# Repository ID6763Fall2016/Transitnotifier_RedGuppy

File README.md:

# Transitnotifier_RedGuppy

This is the transit notifier project called Buzz Clock.
You will need the following hardware and software to build the Buzz Clock: 

Hardware:
<ul>
<li>ESP8266 x 1 (adafruit Huzzah breakout for the PCB we used)</li> 
<li>NeoPixel strip x 1 (60 neoPixels.  You can use less but you'll need to modify the code heavily)</li>
<li>Battery x 1 (or a USB 5 volt power supply with power and ground connections</li>
<li>Resistor x 2 (10k and 470R)</li>
<li>Capacitor x 1 (1000U 16v or 24v) </li>
<li>Push button x 1</li>
</ul>

Software:
<ul>
<li>Adafruit NeoPixel library</li>
<li>WiFi Client Secure library</li>
<li>TinyXML library</li>
</ul>

The working code resides in the NextBusGT folder. After connecting the hardwares together and connecting ESP8266 to your laptop, you need to modify the code with your wifi SSID and Password then upload the code to the ESP8266 and it will start retrieve the data from the xml provided by http://gtbuses.herokuapp.com.

If you wish to make your own PCB instead of using a breadboard for the setup you can start with our CAD files in the WiFiNeoClock director.  We used KiCad to create the board.  Additional information on working with kiCad can be found at..
http://kicad-pcb.org/

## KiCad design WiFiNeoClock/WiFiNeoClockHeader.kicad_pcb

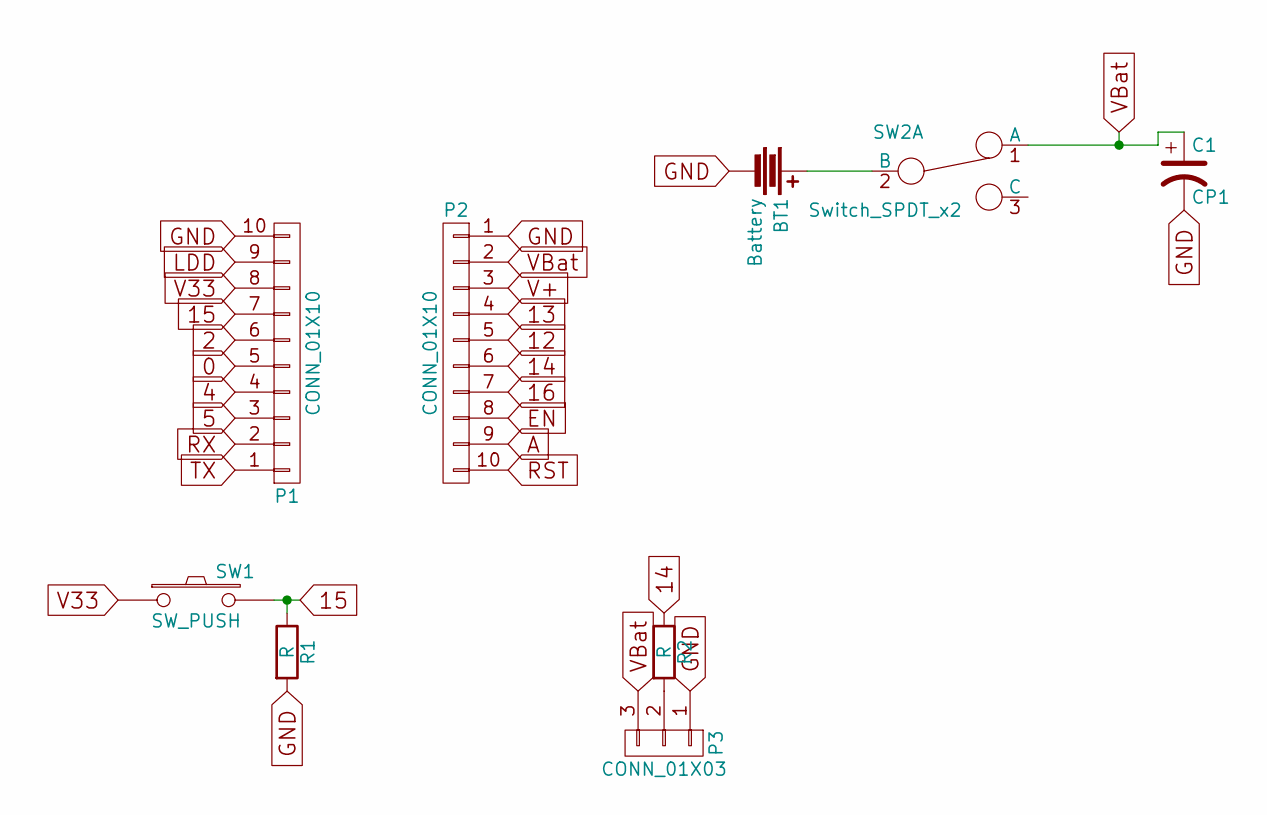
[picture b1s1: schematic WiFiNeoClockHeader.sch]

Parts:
BT1: Battery; Pin_Header_Straight_1x02
C1: CP1; C_Radial_D5_L11_P2.5
P1, P2: CONN_01X10; Pin_Header_Straight_1x10
P3: CONN_01X03; Pin_Header_Straight_1x03
R1, R2: R; Resistor_Horizontal_RM10mm
SW1: SW_PUSH; SW_PUSH_6mm
SW2: Switch_SPDT_x2; SW_NKK_G1xJP

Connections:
0: P1.5
2: P1.6
4: P1.4
5: P1.3
12: P2.5
13: P2.4
14: P2.6, R2.1
15: P1.7, R1.1, SW1.2
16: P2.7
A: P2.9
EN: P2.8
GND: BT1.2, C1.2, P1.10, P2.1, P3.1, R1.2
LDD: P1.9
unnamed: BT1.1, SW2.2 (B)
unnamed: P3.2, R2.2
RST: P2.10
RX: P1.2
TX: P1.1
V33: P1.8, SW1.1
V+: P2.3
VBat: C1.1, P2.2, P3.3, SW2.1 (A)

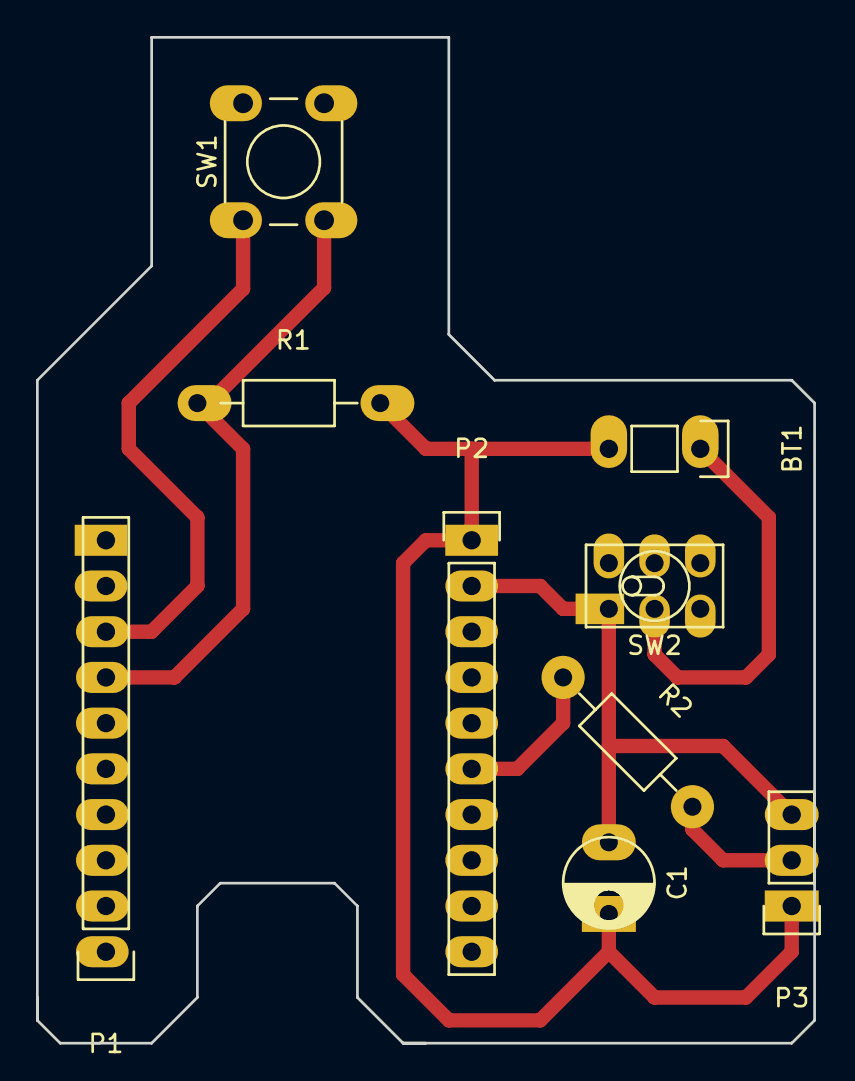
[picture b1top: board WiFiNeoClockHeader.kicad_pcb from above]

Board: 2 copper layers, 43.2 x 55.9 mm, 9 parts (0 on the bottom side), 7 nets.

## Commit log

2016-10-06 Added JSON Stream reading parser with hooks to act on keys
    example of queries for routes and pulling back location info.
2016-10-06 added libraries and examples for JSONstreaming parser
    Should use my version with the modified classes to get stuff done
2016-10-11 Add files via upload
    Design ideas
2016-10-12 Update HTTPSRequest.ino
    add parser
2016-10-12 Add files via upload
    extracts stops from xml
2016-10-12 Added clock starts and version of NextBus to target a specific stop for times
2016-10-13 Created a clock and Got flashing busses on the Neopixels
    Need to figure out a way to cache the bus times while refreshing the
    pixels faster
2016-10-17 "add pcb"
2016-10-18 working with NeoPixels
    working connection between gtbusses and neopixel clock strip
2016-10-18 add new pcb for neoclock
2016-10-21 updated pcb to fix milling errors
    spread out the traces and fixed the drill holes for the Capacitor
2016-10-23 updated kicad files with thicker traces and pads to help with soldering
2016-10-25 Added hooks for button pushes to swap routes
2016-11-01 moved files around to clean up the directory and added the latest code
2016-11-01 added latest cad files for the wifi clock board
2016-11-01 moved the wifi setup testing scripts to deprecated
2016-11-01 added some more specifics based on latest updates
2016-11-01 added image of pcb to readme
2016-11-01 added image of clock
